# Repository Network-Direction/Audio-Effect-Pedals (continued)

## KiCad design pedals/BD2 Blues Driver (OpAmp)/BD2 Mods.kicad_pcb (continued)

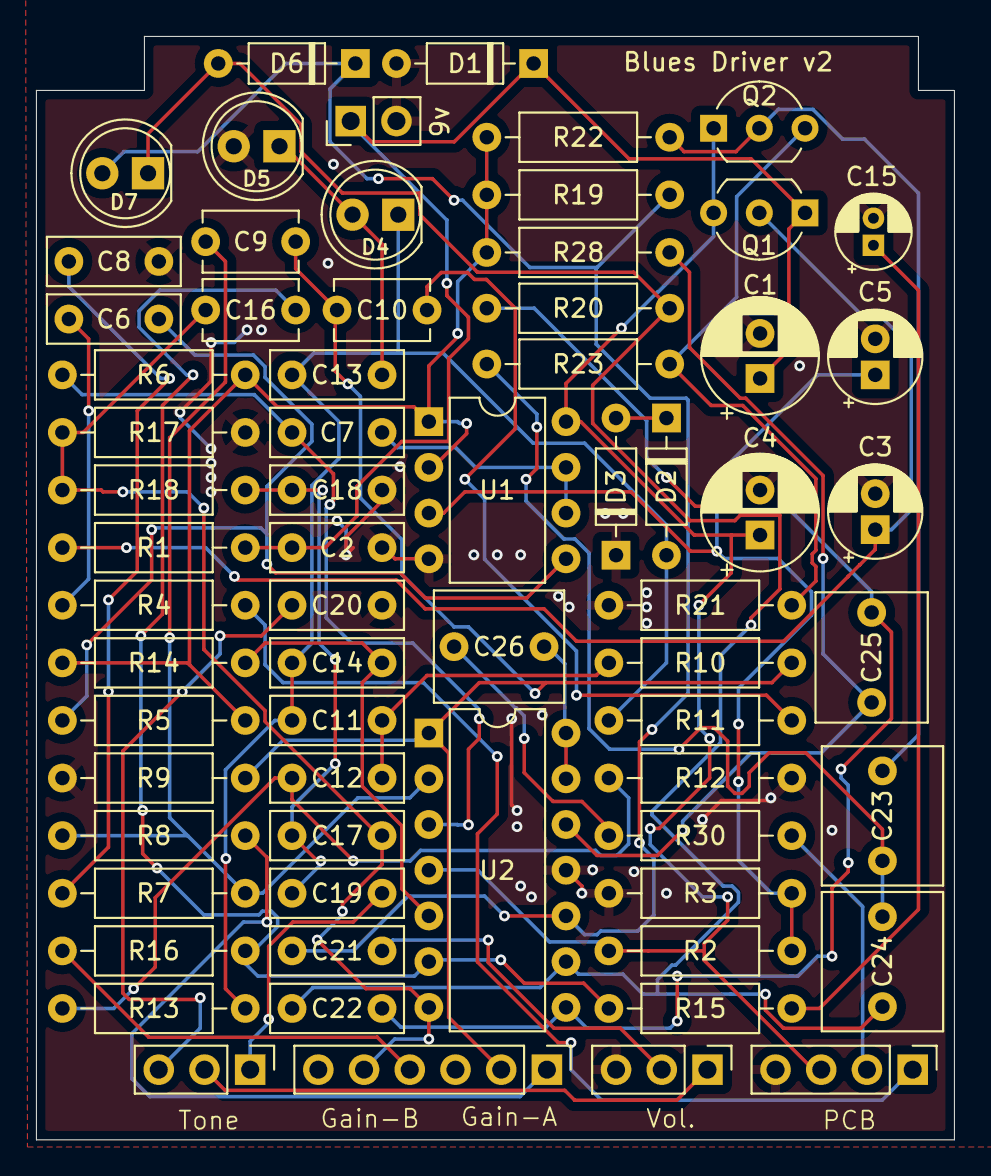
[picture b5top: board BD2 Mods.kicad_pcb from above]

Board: 2 copper layers, 51.0 x 61.3 mm, 67 parts (0 on the bottom side), 41 nets.

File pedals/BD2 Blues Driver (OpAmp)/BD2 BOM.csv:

Reference,Value,Qty
"C1,C4",100uF,2
"C2,C6,C7,C11",100nF,4
"C3,C5",47uF,2
C8,150nF,1
C9,47pF,1
C10,220pF,1
"C12,C20,C21",47nF,3
C13,1nF,1
"C14,C22",2.2nF,2
"C15,C25,C26",1uF,3
C16,100pF,1
"C17,C18,C19",10nF,3
"C23,C24",56nF,2
"D1,D2,D3,D6",1N4148,4
"D4,D5,D7",LED,3
J1,+9v,1
J2,In,1
J4,Out,1
Q1,BC547B,1
Q9,BC547,1
"R1,R9,R17",2K2,3
"R2,R3,R4,R21",10K,4
"R5,R13,R14",1M,3
R6,220K,1
R7,22k,1
R8,22K,1
"R10,R28",100K,2
R11,330K,1
R12,15K,1
R15,4K7,1
R16,33K,1
R18,5K6,1
"R19,R22",470K,2
R20,6K8,1
R23,3K6,1
R30,1K,1
RV1,B100K,1
RV3,10KB,1
RV4,100KA,1
U1,TL072,1
U2,TL074,1

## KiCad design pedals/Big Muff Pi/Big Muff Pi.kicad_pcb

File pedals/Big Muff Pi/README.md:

# Big Muff Pi

## Status
Schematic has been tested. PCB has been built, but updated since the last build.

## Links
https://electrosmash.com/big-muff-pi-analysis

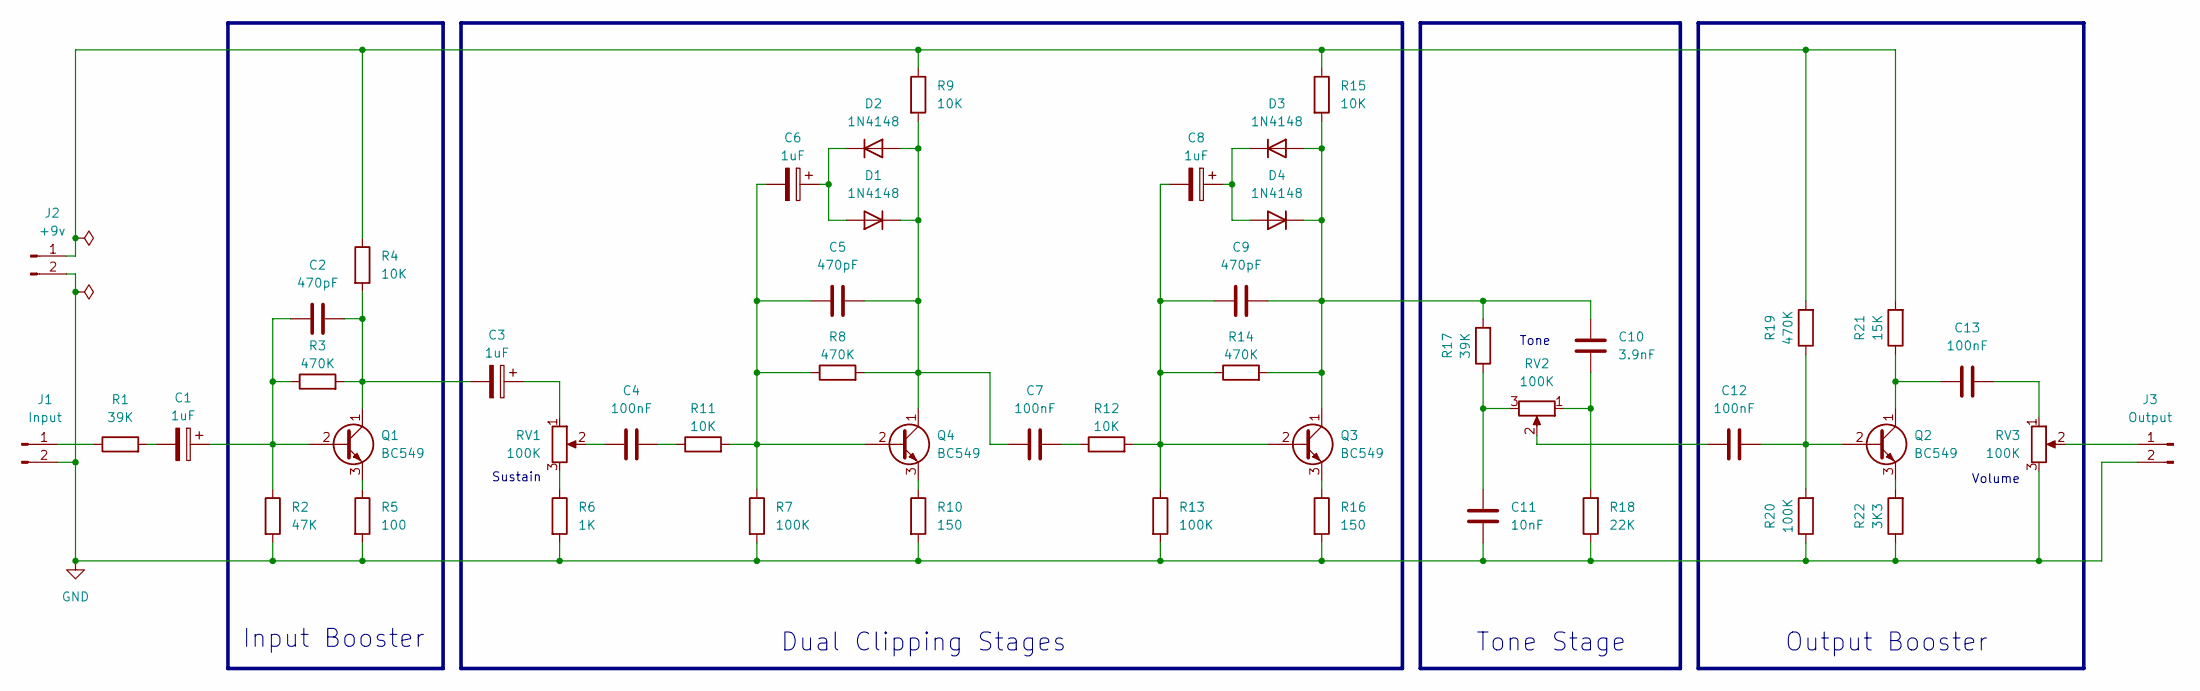
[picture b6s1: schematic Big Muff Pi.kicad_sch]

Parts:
C1, C3, C6, C8: 1uF; CP_Radial_D5.0mm_P2.50mm
C2, C5, C9: 470pF; C_Disc_D3.8mm_W2.6mm_P2.50mm
C4, C7, C12, C13: 100nF; C_Rect_L9.0mm_W5.1mm_P7.50mm_MKT
C10: 3.9nF; C_Rect_L9.0mm_W5.1mm_P7.50mm_MKT
C11: 10nF; C_Rect_L9.0mm_W5.1mm_P7.50mm_MKT
D1, D2, D3, D4: 1N4148; D_DO-35_SOD27_P7.62mm_Horizontal
J1: Input; PinSocket_1x02_P2.54mm_Vertical
J2: +9v; PinSocket_1x02_P2.54mm_Vertical
J3: Output; PinSocket_1x02_P2.54mm_Vertical
Q1, Q2, Q3, Q4: BC549; TO-92_Inline
R1, R17: 39K; R_Axial_DIN0207_L6.3mm_D2.5mm_P10.16mm_Horizontal
R2: 47K; R_Axial_DIN0207_L6.3mm_D2.5mm_P10.16mm_Horizontal
R3, R8, R14, R19: 470K; R_Axial_DIN0207_L6.3mm_D2.5mm_P10.16mm_Horizontal
R4, R9, R11, R12, R15: 10K; R_Axial_DIN0207_L6.3mm_D2.5mm_P10.16mm_Horizontal
R5: 100; R_Axial_DIN0207_L6.3mm_D2.5mm_P10.16mm_Horizontal
R6: 1K; R_Axial_DIN0207_L6.3mm_D2.5mm_P10.16mm_Horizontal
R7, R13, R20: 100K; R_Axial_DIN0207_L6.3mm_D2.5mm_P10.16mm_Horizontal
R10, R16: 150; R_Axial_DIN0207_L6.3mm_D2.5mm_P10.16mm_Horizontal
R18: 22K; R_Axial_DIN0207_L6.3mm_D2.5mm_P10.16mm_Horizontal
R21: 15K; R_Axial_DIN0207_L6.3mm_D2.5mm_P10.16mm_Horizontal
R22: 3K3; R_Axial_DIN0207_L6.3mm_D2.5mm_P10.16mm_Horizontal
RV1, RV2, RV3: 100K; PinSocket_1x03_P2.54mm_Vertical

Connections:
GND: C11.1, J1.2, J2.2, J3.2, R2.2, R5.2, R6.2, R7.2, R10.2, R13.2, R16.2, R18.1, R20.1, R22.1, RV3.3
unnamed: C1.2, R1.2
unnamed: C3.1, RV1.1
unnamed: C4.1, RV1.2
unnamed: C4.2, R11.1
unnamed: C7.2, R12.1
unnamed: C10.1, R18.2, RV2.1
unnamed: C11.2, R17.1, RV2.3
unnamed: C12.2, RV2.2
unnamed: C13.1, RV3.1
unnamed: C6.1, D1.2 (A), D2.1 (K)
unnamed: C5.2, C7.1, D1.1 (K), D2.2 (A), Q4.1 (C), R8.2, R9.2
unnamed: C9.2, C10.2, D3.2 (A), D4.1 (K), Q3.1 (C), R14.2, R15.2, R17.2
unnamed: C8.1, D3.1 (K), D4.2 (A)
unnamed: J1.1, R1.1
unnamed: J2.1, R4.1, R9.1, R15.1, R19.2, R21.2
unnamed: J3.1, RV3.2
unnamed: C1.1, C2.1, Q1.2 (B), R2.1, R3.1
unnamed: C2.2, C3.2, Q1.1 (C), R3.2, R4.2
unnamed: Q1.3 (E), R5.1
unnamed: C12.1, Q2.2 (B), R19.1, R20.2
unnamed: C13.2, Q2.1 (C), R21.1
unnamed: Q2.3 (E), R22.2
unnamed: C8.2, C9.1, Q3.2 (B), R12.2, R13.1, R14.1
unnamed: Q3.3 (E), R16.1
unnamed: C5.1, C6.2, Q4.2 (B), R7.1, R8.1, R11.2
unnamed: Q4.3 (E), R10.1
unnamed: R6.1, RV1.3

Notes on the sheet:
Output Booster
Tone Stage
Volume
Sustain
Dual Clipping Stages
Input Booster
Tone

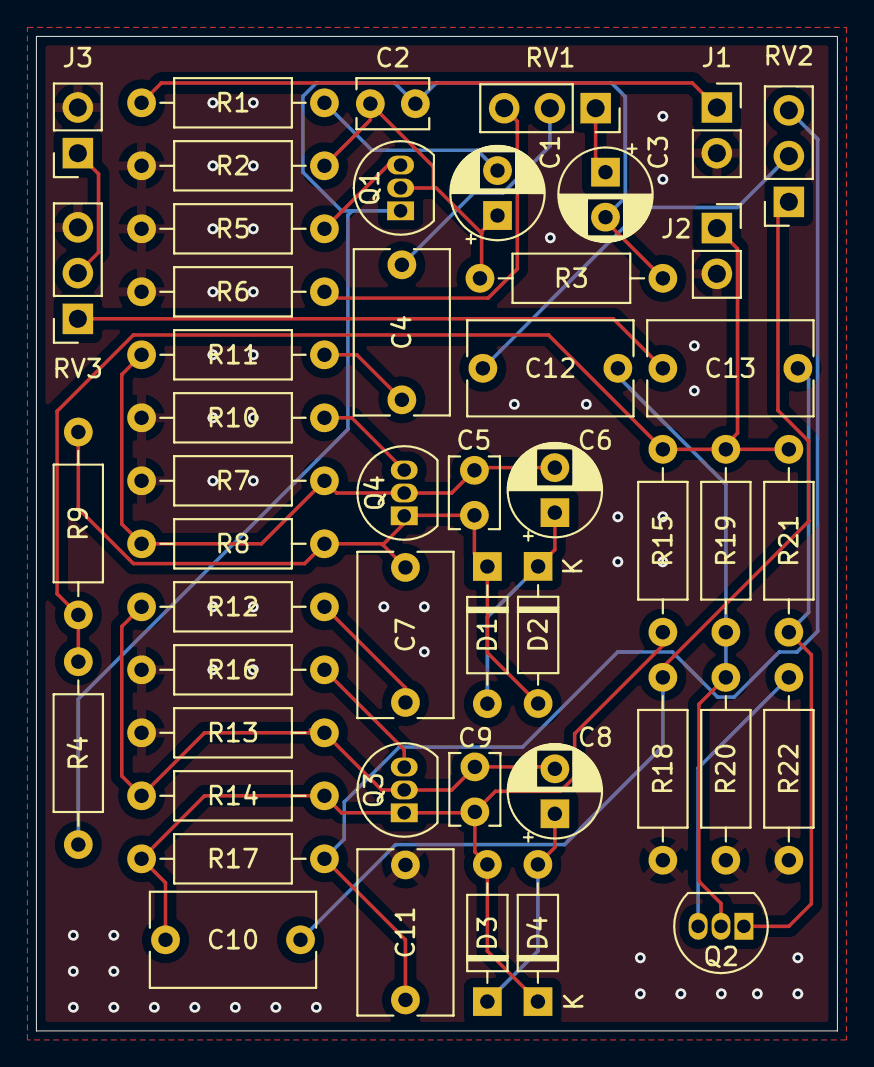
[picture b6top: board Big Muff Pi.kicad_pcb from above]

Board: 2 copper layers, 44.5 x 55.2 mm, 49 parts (0 on the bottom side), 28 nets.

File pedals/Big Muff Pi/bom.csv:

"Reference","Value","Datasheet","Footprint","Qty","DNP"
"C1,C3,C6,C8","1uF","~","Capacitor_THT:CP_Radial_D5.0mm_P2.50mm","4",""
"C2,C5,C9","470pF","~","Capacitor_THT:C_Disc_D3.8mm_W2.6mm_P2.50mm","3",""
"C4,C7,C12,C13","100nF","~","Capacitor_THT:C_Rect_L9.0mm_W5.1mm_P7.50mm_MKT","4",""
"C10","3.9nF","~","Capacitor_THT:C_Rect_L9.0mm_W5.1mm_P7.50mm_MKT","1",""
"C11","10nF","~","Capacitor_THT:C_Rect_L9.0mm_W5.1mm_P7.50mm_MKT","1",""
"D1,D2,D3,D4","1N4148","https://assets.nexperia.com/documents/data-sheet/1N4148_1N4448.pdf","Diode_THT:D_DO-35_SOD27_P7.62mm_Horizontal","4",""
"J1","Input","~","Connector_PinSocket_2.54mm:PinSocket_1x02_P2.54mm_Vertical","1",""
"J2","+9v","~","Connector_PinSocket_2.54mm:PinSocket_1x02_P2.54mm_Vertical","1",""
"J3","Output","~","Connector_PinSocket_2.54mm:PinSocket_1x02_P2.54mm_Vertical","1",""
"Q1,Q2,Q3,Q4","BC549","https://www.onsemi.com/pub/Collateral/BC550-D.pdf","Package_TO_SOT_THT:TO-92_Inline","4",""
"R1,R17","39K","~","Resistor_THT:R_Axial_DIN0207_L6.3mm_D2.5mm_P10.16mm_Horizontal","2",""
"R2","47K","~","Resistor_THT:R_Axial_DIN0207_L6.3mm_D2.5mm_P10.16mm_Horizontal","1",""
"R3,R8,R14,R19","470K","~","Resistor_THT:R_Axial_DIN0207_L6.3mm_D2.5mm_P10.16mm_Horizontal","4",""
"R4,R9,R11,R12,R15","10K","~","Resistor_THT:R_Axial_DIN0207_L6.3mm_D2.5mm_P10.16mm_Horizontal","5",""
"R5","100","~","Resistor_THT:R_Axial_DIN0207_L6.3mm_D2.5mm_P10.16mm_Horizontal","1",""
"R6","1K","~","Resistor_THT:R_Axial_DIN0207_L6.3mm_D2.5mm_P10.16mm_Horizontal","1",""
"R7,R13,R20,RV1,RV2,RV3","100K","~","-- mixed values --","6",""
"R10,R16","150","~","Resistor_THT:R_Axial_DIN0207_L6.3mm_D2.5mm_P10.16mm_Horizontal","2",""
"R18","22K","~","Resistor_THT:R_Axial_DIN0207_L6.3mm_D2.5mm_P10.16mm_Horizontal","1",""
"R21","15K","~","Resistor_THT:R_Axial_DIN0207_L6.3mm_D2.5mm_P10.16mm_Horizontal","1",""
"R22","3K3","~","Resistor_THT:R_Axial_DIN0207_L6.3mm_D2.5mm_P10.16mm_Horizontal","1",""

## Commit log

2024-11-11 Create etst
2024-11-11 Initial upload
2024-11-11 Added enclosure Files
2024-11-12 Fixed a mistake on the input stage
2024-11-17 Cap change in the gyrator
    56nF caps are hard to find now, so added an alternative of 47nF or 68nF
2024-11-17 Create MXR Distortion
2024-11-24 Create test
2024-11-24 Update and rename test to 1. Comparitors and Hysteresis
2024-11-24 Rename 1. Comparitors and Hysteresis to 1. Comparitors and Hysteresis.md
2024-11-24 Rename Schmitt Trigger.md to 2. Schmitt Trigger.md
2024-11-24 Rename audio circuit blocks/1. Comparitors and Hysteresis.md to audio circuit blocks/1. Op Amps/Hysteresis.md
2024-11-24 Rename Hysteresis.md to Hysteresis.md
2024-11-24 Rename Hysteresis.md to 5. Hysteresis.md
2024-11-24 Rename audio circuit blocks/2. Schmitt Trigger.md to audio circuit blocks/1. OpAmps/6. Schmitt Trigger.md
2024-11-24 Rename audio circuit blocks/3. Relaxation Oscillators.md to audio circuit blocks/2. Oscillators/1. Relaxation Oscillators.md
2024-12-03 Rename 3. Envelope.md to 4. Envelope.md
2024-12-03 Rename 2. Filters.md to 3. Filters.md
2024-12-03 Update 2. Frequencies.md
    Added information about phase
2024-12-03 Update 3. Filters.md
    Added a note on all pass filters
2024-12-03 Added All Pass Filter section
2024-12-04 Updated all pass filter
2024-12-04 Updated the All Pass Filter section
2024-12-11 Sampling Rate
    Added a section on samples and sampling rate
2024-12-13 Added anti-aliasing methods
2024-12-13 Added an anti-aliasing circuit
2024-12-14 Added interrupts
2024-12-15 Rename 3. Arduino ADC.md to 4. Arduino ADC.md
2025-03-05 Renamed folders
2025-03-05 Created files for buffers
2025-03-08 Renamed a few folders and files
2025-03-14 Create 7. Opamp Types
2025-03-14 Update 7. Opamp Types
2025-03-14 rename
